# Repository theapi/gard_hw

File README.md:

# GARD STM32 Hardware

The Garden Animal Repellent Device built with an  STM32L053C8Tx and LoRa RFM95 module.

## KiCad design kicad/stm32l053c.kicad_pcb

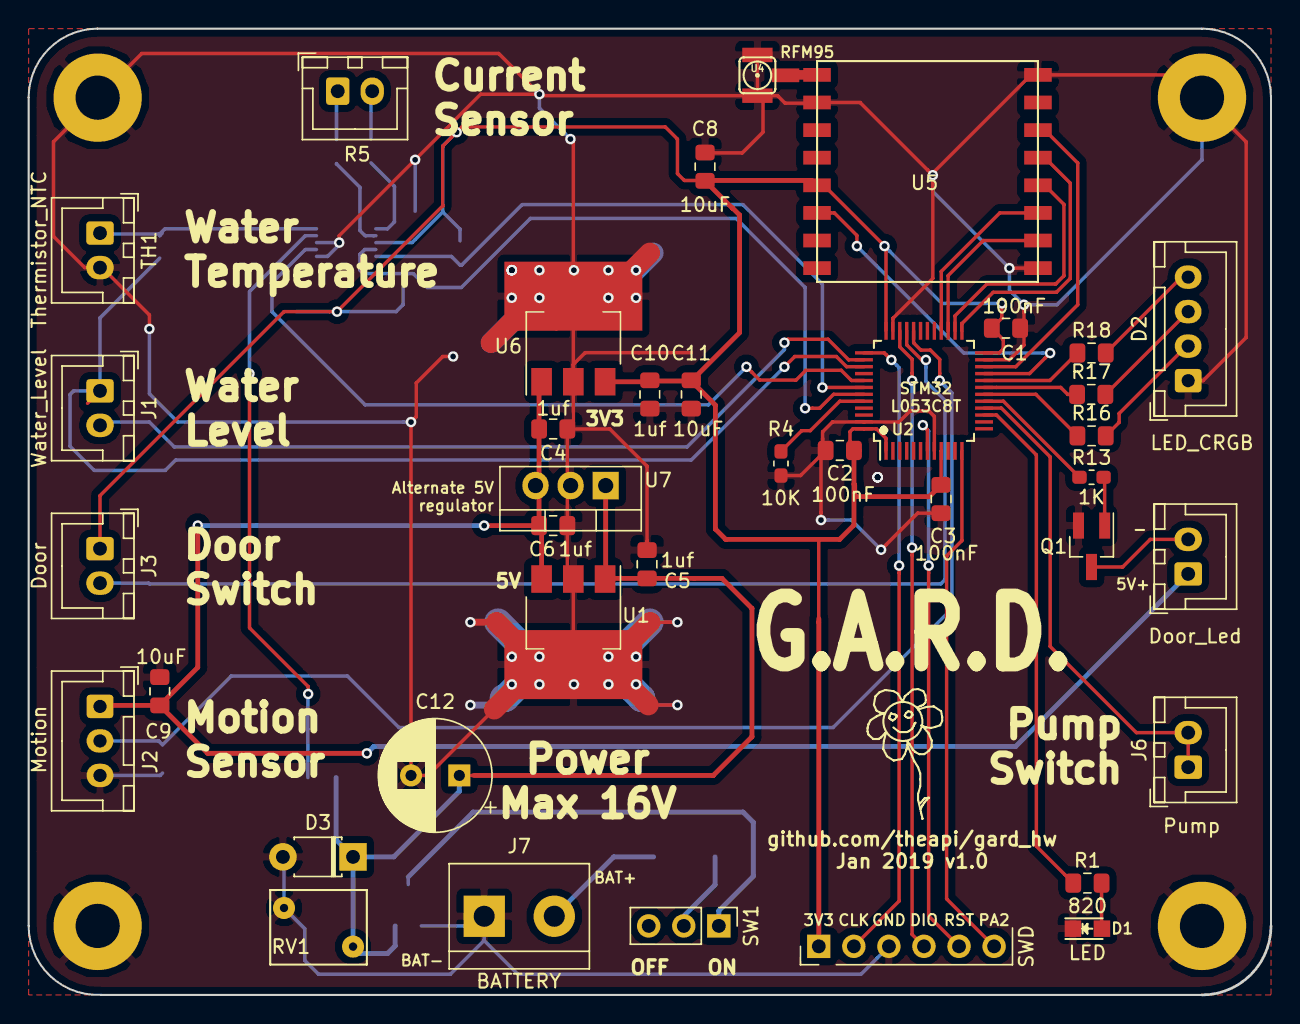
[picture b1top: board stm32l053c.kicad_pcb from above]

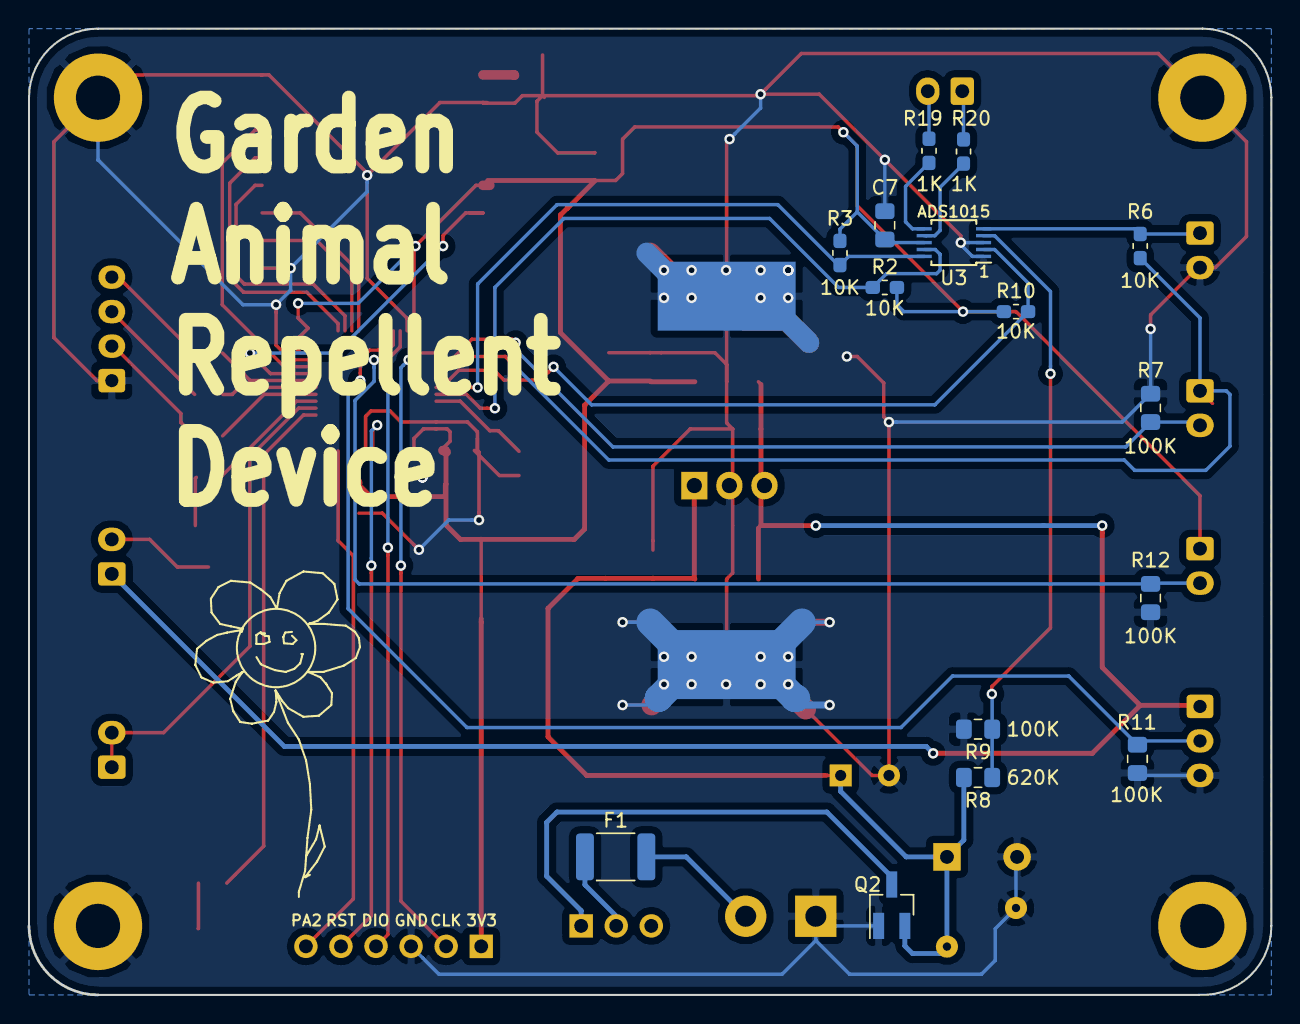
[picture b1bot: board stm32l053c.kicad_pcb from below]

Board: 2 copper layers, 90.0 x 70.0 mm, 57 parts (15 on the bottom side), 44 nets.

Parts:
C1, C2, C3: 100nF; C_0805_2012Metric_Pad1.15x1.40mm_HandSolder
C4, C5, C6, C10: 1uf; C_0805_2012Metric_Pad1.15x1.40mm_HandSolder
C7, C8, C9, C11: 10uF; C_0805_2012Metric_Pad1.15x1.40mm_HandSolder
C12: CP; CP_Radial_D8.0mm_P3.50mm
D1: LED; LED_0805
D2: LED_CRGB; JST_XH_B04B-XH-A_1x04_P2.50mm_Vertical
D3: 16V; D_T-1_P5.08mm_Horizontal
F1: Polyfuse; R_1812_4532Metric_Pad1.30x3.40mm_HandSolder
H1, H2, H3, H4: MountingHole_Pad; MountingHole_3.2mm_M3_Pad
J1: Water_Level; JST_XH_B02B-XH-A_1x02_P2.50mm_Vertical
J2: Motion; JST_XH_B03B-XH-A_1x03_P2.50mm_Vertical
J3: Door; JST_XH_B02B-XH-A_1x02_P2.50mm_Vertical
J4: Door_Led; JST_XH_B02B-XH-A_1x02_P2.50mm_Vertical
J6: Pump; JST_XH_B02B-XH-A_1x02_P2.50mm_Vertical
J7: BATTERY; TerminalBlock_bornier-2_P5.08mm
P1: SWD; Pin_Header_Straight_1x06_Pitch2.54mm
Q1: Q_NMOS_GSD; SOT-23_Handsoldering
Q2: Q_PMOS_GSD; SOT-23_Handsoldering
R1, R16, R17, R18: 820; R_0805_2012Metric_Pad1.15x1.40mm_HandSolder
R2, R3, R4, R6, R10: 10K; R_0603_1608Metric_Pad1.05x0.95mm_HandSolder
R5: 0.01R; JST_XH_B02B-XH-A_1x02_P2.50mm_Vertical
R7, R9, R11, R12: 100K; R_0805_2012Metric_Pad1.15x1.40mm_HandSolder
R8: 620K; R_0805_2012Metric_Pad1.15x1.40mm_HandSolder
R13, R19, R20: 1K; R_0603_1608Metric_Pad1.05x0.95mm_HandSolder
RV1: 18V; RV_Disc_D7mm_W5.4mm_P5mm
SW1: SW_Push_SPDT; PinHeader_1x03_P2.54mm_Vertical
TH1: Thermistor_NTC; JST_XH_B02B-XH-A_1x02_P2.50mm_Vertical
U1: MCP1703A-5002_SOT223; SOT-223-3_TabPin2_heatsink
U2: STM32L053C8_LQFP48; LQFP-48_7x7mm_Pitch0.5mm
U3: ADS1015; TSSOP-10_3x3mm_P0.5mm
U4: UFL_SMA; coaxial_u.fl-r-smt-1
U5: RFM92/95; RFM92_95_96_98
U6: MCP1703A-3302_SOT223; SOT-223-3_TabPin2_heatsink
U7: LP2954_TO220; TO-220-3_Vertical

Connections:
+3V3: C1.1, C2.1, C3.1, C7.1, C8.1, C10.1, C11.1, J3.1, P1.1, R2.1, R3.1, R10.1, U2.1, U2.9, U2.24, U2.36, U2.48, U3.8, U5.13, U6.3
+5V: C4.1, C6.1, C9.1, J2.1, J4.1, U1.3, U6.1, U7.3
+BATT: F1.2, J7.2
/AIN2: R19.1, U3.6
/AIN3: R20.1, U3.7
/BATT: C5.1, C12.1, D3.1, Q2.2, R8.2, RV1.1, U1.1, U7.1
/BATT_V: R8.1, R9.1, U3.4
/BOOT0: R4.1, U2.44
ADC_RDY: R10.2, U2.41, U3.2
ANT: U4.1, U5.9
DIO0: U2.21, U5.14
DOOR: J3.2, R12.1, U2.33
DOOR_LED: R13.1, U2.17
Earth: C1.2, C2.2, C3.2, C4.2, C5.2, C6.2, C7.2, C8.2, C9.2, C10.2, C11.2, C12.2, D1.1, D2.1, D3.2, H1.1, H2.1, H3.1, H4.1, J2.3, J7.1, P1.3, Q1.2, Q2.1, R4.2, R7.2, R9.2, R11.2, R12.2, RV1.2, TH1.2, U1.2, U2.8, U2.23, U2.35, U2.47, U3.1, U3.3, U4.2, U5.1, U5.8, U5.10, U6.2, U7.2
I2C1_SCL: R3.2, U2.42, U3.10
I2C1_SDA: R2.2, U2.43, U3.9
LED: R1.1, U2.15
LED_BLUE: R18.1, U2.20
LED_GREEN: R17.1, U2.19
LED_RED: R16.1, U2.18
MOTION: J2.2, R11.1, U2.32
NRST: P1.5, U2.7
unnamed: D1.2, R1.2
unnamed: D2.2, R16.2
unnamed: D2.3, R17.2
unnamed: D2.4, R18.2
unnamed: F1.1, SW1.2
unnamed: J4.2, Q1.3
unnamed: Q1.1, R13.2
unnamed: Q2.3, SW1.1
unnamed: R5.2, R19.2
unnamed: R5.1, R20.2
PUMP: J6.1, J6.2, U2.16
RFM_RST: U2.22, U5.6
SENSOR_PWR: J1.1, R6.1, U2.39
SPI2_MISO: U2.27, U5.2
SPI2_MOSI: U2.28, U5.3
SPI2_NSS: U2.25, U5.5
SPI2_SCK: U2.26, U5.4
SWCLK: P1.2, U2.37
SWDIO: P1.4, U2.34
USART2_TX: P1.6, U2.12
WATER_LEVEL: J1.2, R7.1, U2.38
WATER_TEMP: R6.2, TH1.1, U3.5

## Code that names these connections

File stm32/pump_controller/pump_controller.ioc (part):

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Mcu.Name=STM32L053C(6-8)Tx
Mcu.Package=LQFP48
Mcu.UserName=STM32L053C8Tx
PA11.GPIOParameters=GPIO_Label
PA11.GPIO_Label=MOTION
PA11.Signal=GPIO_Input
PA12.GPIOParameters=GPIO_Label
PA12.GPIO_Label=DOOR
PA12.Signal=GPXTI12
PA13.Mode=Serial_Wire
PA13.Signal=SYS_SWDIO
PA14.Mode=Serial_Wire
PA14.Signal=SYS_SWCLK
PA15.GPIOParameters=GPIO_Label
PA15.GPIO_Label=WATER_LEVEL
PA15.Signal=GPIO_Input
PA2.Mode=Asynchronous
PA2.Signal=USART2_TX
PA3.Mode=Asynchronous
PA3.Signal=USART2_RX
PA5.GPIOParameters=GPIO_Label
PA5.GPIO_Label=LED
PA5.Signal=GPIO_Output
PA6.GPIOParameters=GPIO_Label
PA6.GPIO_Label=PUMP
PA6.Signal=GPIO_Output
PA7.GPIOParameters=GPIO_Label
PA7.GPIO_Label=DOOR_LED
PA7.Signal=GPIO_Output
PB0.GPIOParameters=GPIO_Label
PB0.GPIO_Label=LED_RED
PB0.Signal=GPIO_Output
PB1.GPIOParameters=GPIO_Label
PB1.GPIO_Label=LED_GREEN
PB1.Signal=GPIO_Output
PB10.GPIOParameters=GPIO_Label
PB10.GPIO_Label=DIO0
PB10.Signal=GPXTI10
PB11.GPIOParameters=GPIO_Label
PB11.GPIO_Label=RFM_RESET
PB11.Signal=GPIO_Output
PB12.GPIOParameters=GPIO_Label
PB12.GPIO_Label=SPI2_CS
PB12.Signal=GPIO_Output
PB13.Mode=Full_Duplex_Master
PB13.Signal=SPI2_SCK
PB14.Mode=Full_Duplex_Master
PB14.Signal=SPI2_MISO
PB15.Mode=Full_Duplex_Master
PB15.Signal=SPI2_MOSI
PB2.GPIOParameters=GPIO_Label
PB2.GPIO_Label=LED_BLUE
PB2.Signal=GPIO_Output
PB3.GPIOParameters=GPIO_Label
PB3.GPIO_Label=SENSOR_PWR
PB3.Signal=GPIO_Output
PB5.GPIOParameters=GPIO_Label
PB5.GPIO_Label=ADC_RDY
PB5.Signal=GPXTI5
PB6.Mode=I2C
PB6.Signal=I2C1_SCL
PB7.Mode=I2C
PB7.Signal=I2C1_SDA
RCC.HSE_VALUE=8000000
RCC.SYSCLKFreq_VALUE=2097000
board=lora_sensor

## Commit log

2018-12-26 Start of pin assignment
2018-12-26 Schematic
2018-12-26 Start of layout
2018-12-27 5V regulator before the 3V3 one
2018-12-27 Two voltage regulator layout
2018-12-27 Protection
2018-12-27 Solder mask for the ADS1015
2018-12-28 Power layout
2018-12-28 Changed the overvoltage protection
2018-12-28 Reassign ADC pins
2018-12-29 Moved the ADC
2018-12-29 All connected
2018-12-29 Power switch
2018-12-29 Labels
2018-12-31 Altenate 5V regulator
2018-12-31 Heatsinking for the 5V regulator
2018-12-31 Logos
2018-12-31 Board image
2018-12-31 Antenna datasheet
2018-12-31 Name on the board
2019-01-01 Solder mask print
2019-01-02 Gerbers
2019-01-03 Heatsinked vreg
2019-01-03 Removed old gerbers
2019-01-03 Updated image
2019-01-03 Ordered from JLCPCB
2019-01-10 Renamed
2019-01-12 Blinking leds
2019-01-13 Cap value
2019-01-13 ADS1015 ADC
2019-01-15 Buttons
2019-01-16 WATER_Temperature()
2019-01-16 Door led controlled by door switch
2019-01-19 All outputs
2019-01-22 Battery mV calibration
2019-01-29 Water temperature
2019-01-30 Steinhart–Hart equation
2019-01-30 Allow for negative temperatures
2019-01-31 Water temperature as a float
